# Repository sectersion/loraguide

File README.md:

# loraguide

Hello! In this guide, you will create a custom Meshtastic-enabled LORA board with a microcontroller, antenna, radio chip, and other things.

## First things first

To start your project, we need to download KiCad. KiCad is an open-source software for designing circuit boards, or PCBs. We can use the terms interchangably.

Go to https://www.kicad.org/download/ and install the version for your OS. After that finishes, create a new project. Name it anything you want, but I will name mine Loraguide.

After that finishes, you should be on a screen that looks like this: 

# The Schematic

The first step to designing a circuit board is the schematic. A schematic is essentially a wiring diagram, to show which components connect to what. That means it is very important that we follow a few design rules when creating our schematic:

 - Power symbols always point up
 - Ground symbols always point down
 - Net labels can be used instead of wires

First, click **Schematic Editor** on the main project page. Hit the **A** key to open the symbol chooser. Search "esp32-s3" and select the **ESP32-S3-WROOM-1**.

Place it in the middle. Next, search for the **SX1262** radio chip and place it to the left of the ESP32.

## Power system

### Organization
To keep things clean, use **Power Symbols** instead of drawing wires everywhere. Hit **P**, type +3V3, and place it on the 3V3 pin of the ESP32. Do the same for GND.

### Power input
Search for "USB_C_Receptacle_USB2.0_14P". 

Connect the GND pins to a GND power symbol. **Note on the SHIELD pins:** Do not connect these directly to GND. This can feed RF noise back into your host computer. For this project, leave the shield pins isolated or connected to a separate chassis pad if available.

Connect **VBUS** to a **+5V** power symbol. Place two **5.1k ohm** resistors (R_Small) on the **CC1** and **CC2** pins and connect the other ends to GND. This ensures your USB-C charger provides the correct 5V.

## SX1262 Power & RF

### Power Decoupling
Chips draw sudden bursts of current. Decoupling capacitors (100nF and 10µF) act as local water tanks, sitting right next to the chip to handle these bursts.

Connect **VDD_IN** to **+3V3** and place one **100nF** and one **10µF** capacitor between that line and GND.

### The DCC_SW Inductor
The SX1262 has an internal DC-DC converter that requires a **15µH inductor** on the **DCC_SW** pin. This inductor needs special care; it is a switching component right next to the radio. On the PCB, it must be placed as close as possible to the pin.

### RF Output Matching
Simply running a wire to the antenna is inefficient and can be illegal because it emits harmonics. You need a **matching network** (filtering) on the RF output. This usually involves a series inductor and capacitors to GND between the **RFO** pin and the antenna connector.

| Pin | What to do: |
|---|---|
| VDD_IN | Decouple with 100nF and 10µF |
| VBAT | Draw a direct wire to VDD_IN |
| VBAT_IO | Decouple with one 100nF capacitor |
| VREG | Decouple with one 100nF capacitor |
| DCC_SW | Connect 15µH inductor |
| VR_PA | 100nF capacitor to GND (DO NOT connect to 3.3V) |
| GND | Connect directly to GND |

### 5V to 3.3V conversion
Use an **AMS1117-3.3** LDO regulator to convert the 5V from USB to the 3.3V our chips need.

| Pin | Connection |
|-----|-----------|
| VIN | +5V from VBUS + 10µF cap to GND |
| VOUT | +3V3 + 10µF cap to GND |
| GND | GND |

## USB Data, Buttons, and SPI

### USB Data Lines
Connect the **D+** and **D-** pins of the USB connector to the **USB Data + and -** pins on the ESP32. Use **Net Labels (L)** to keep the wires from crossing.

### Boot and Reset Buttons
Both the **EN** (Reset) and **GPIO0** (Boot) pins need a **10kΩ pull-up resistor** to 3.3V. Connect push buttons that pull these pins to GND when pressed.

### SPI & Control Wiring
| Signal | ESP32 Pin | SX1262 Pin |
|--------|-----------|------------|
| SCK    | GPIO5     | SCK        |
| MOSI   | GPIO6     | MOSI       |
| MISO   | GPIO7     | MISO       |
| NSS    | GPIO8     | NSS        |
| RESET  | GPIO3     | RESET      |
| BUSY   | GPIO4     | BUSY       |
| DIO1   | GPIO9     | DIO1       |

# PCB Section

## Footprint Assignment
In **Tools > Assign Footprints**, assign the physical shapes. For resistors and capacitors, **R_0402** or **C_0402** are standard for these boards.

## Placement
1. **ESP32:** Place at the top. Ensure the antenna "keep-out" area is outside the board edge.
2. **SX1262 & U.FL Connector:** Place these very close together.
3. **DCC_SW Inductor:** Place this right against the radio chip pin.
4. **Decoupling Caps:** Place them right next to their respective power pins.

## Routing Order
Sensitive signals must be routed first so they have the cleanest, most direct paths.

1. **RF Trace First:** Shortest path from chip to antenna. Use 45-degree angles.
2. **USB Data Lines:** Route D+ and D- as a pair, keeping them similar in length.
3. **SPI & Control Signals:** Connect the communication lines.
4. **Power Traces:** 3.3V and 5V. Use wider traces (0.5mm) for these.
5. **GND:** Handled by the copper pour.

## Ground Plane and Stitching
Add a **Filled Zone (Z)** for GND on both the top (**F.Cu**) and bottom (**B.Cu**) layers. 

To prevent "floating" ground islands and interference, add **stitching vias**. These are small holes that connect the top and bottom ground planes. Place them around the perimeter of the board and near the RF trace.

## Final Steps
Run the **DRC (Design Rule Check)** to find errors. Export your **Gerbers** and **Drill Files**, zip them up, and upload to a manufacturer like JLCPCB.

You have designed a grounded and RF-safe LoRa board.

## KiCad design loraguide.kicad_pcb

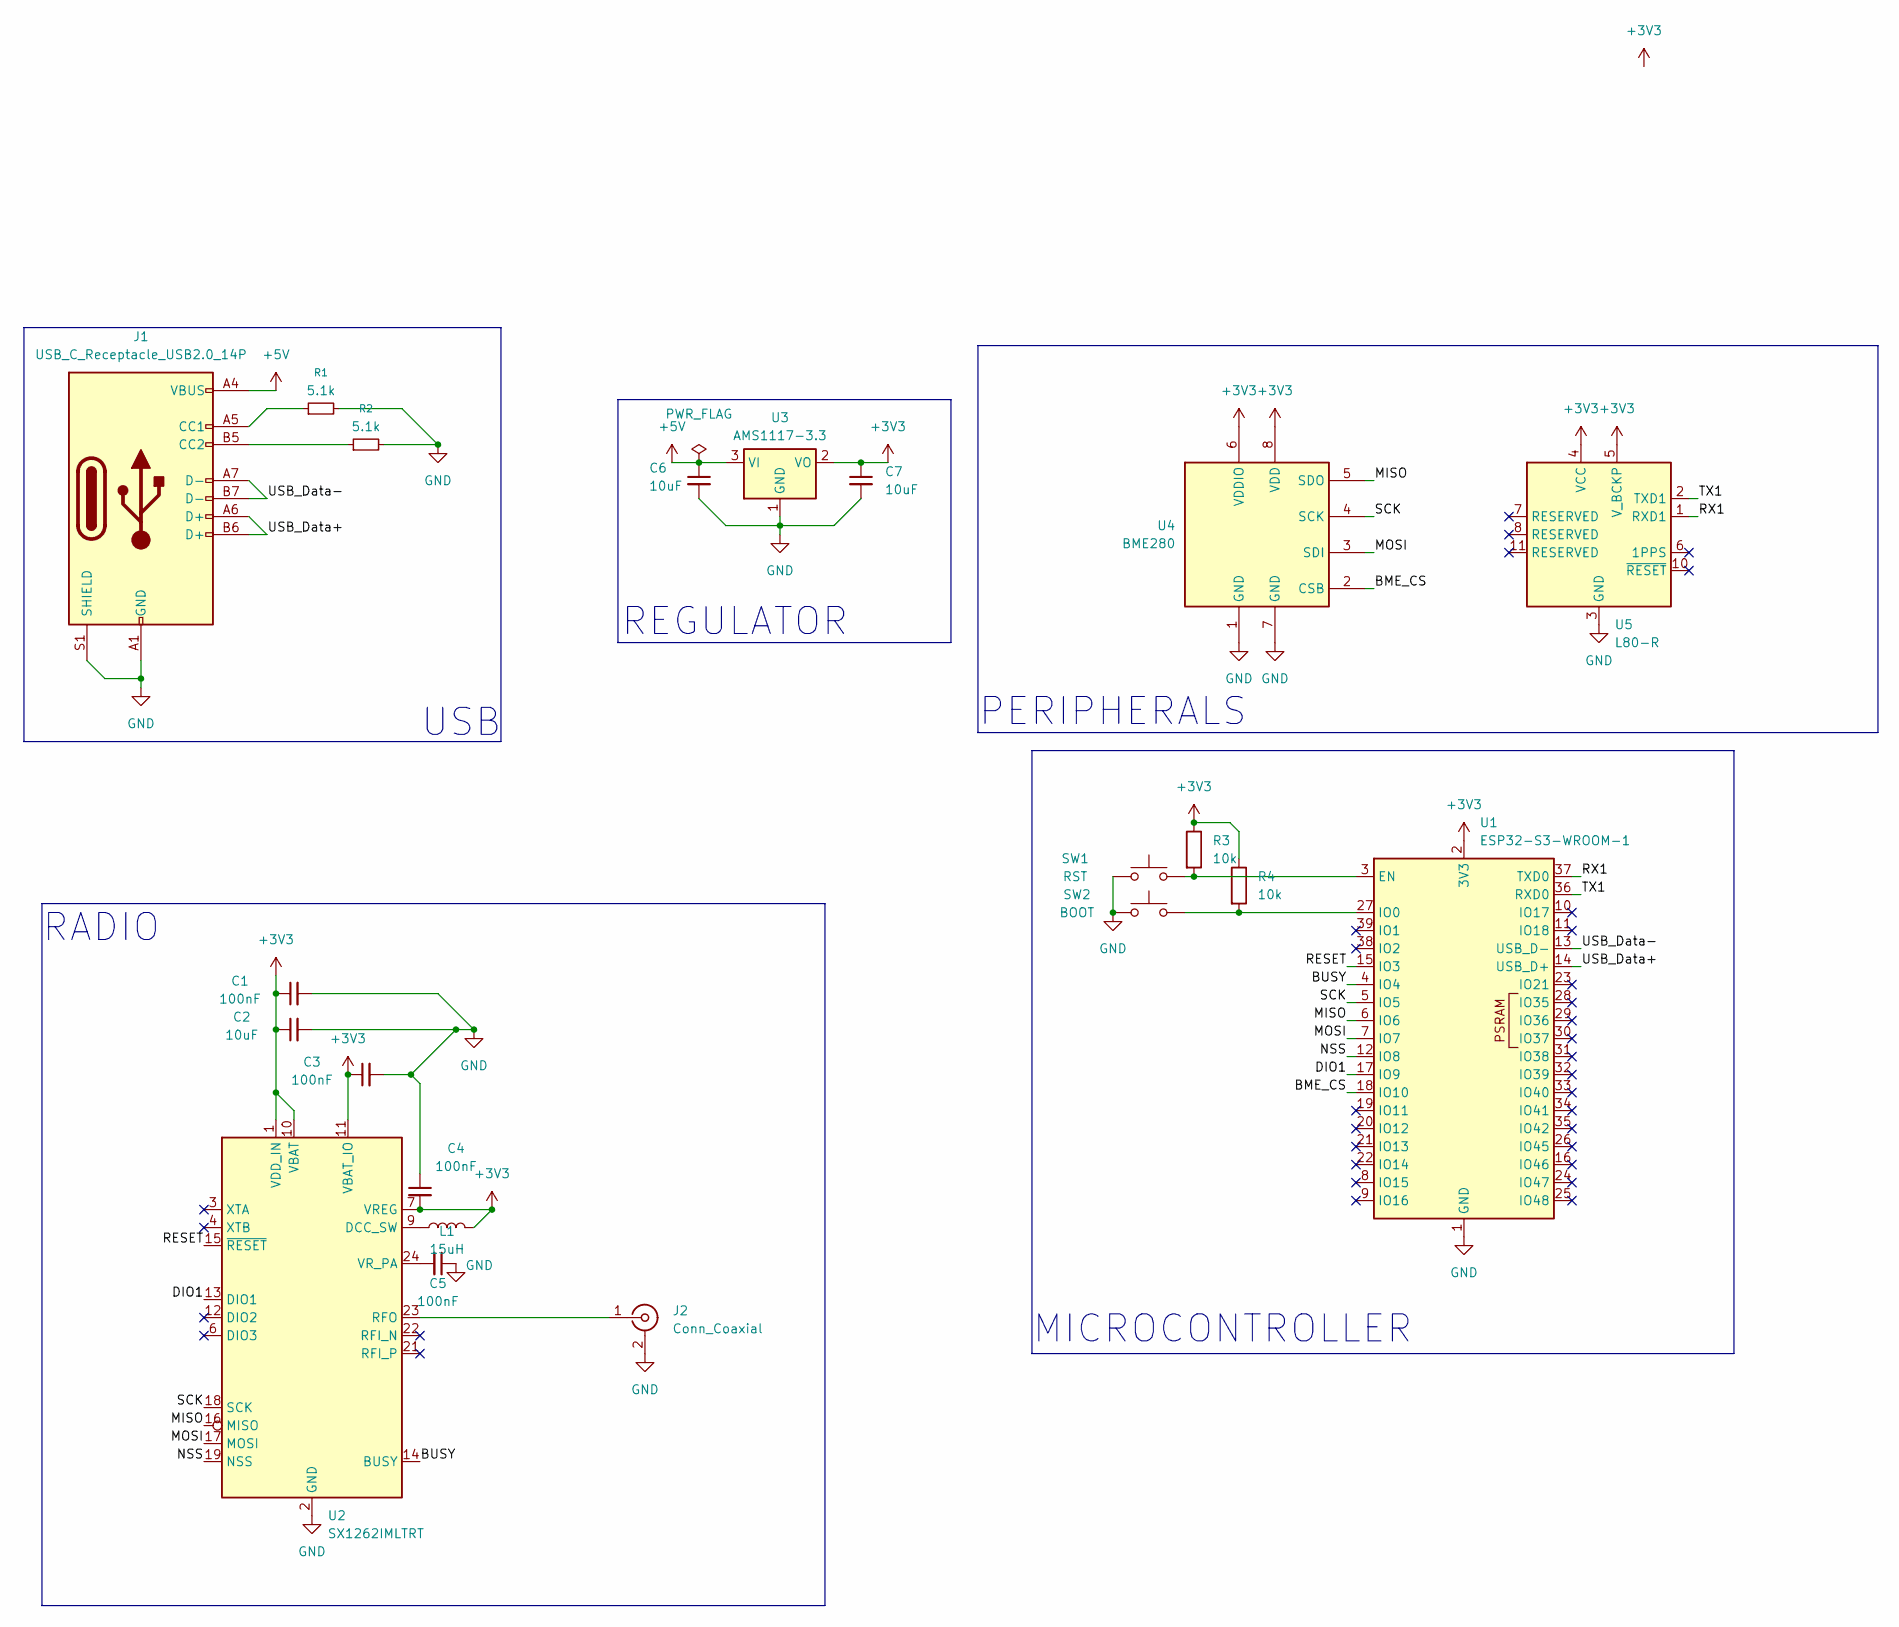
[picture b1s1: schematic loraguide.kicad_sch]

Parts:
C1, C3, C4, C5: 100nF; C_0402_1005Metric
C2, C6, C7: 10uF; C_0402_1005Metric
J1: USB_C_Receptacle_USB2.0_14P; USB_C_Receptacle_GCT_USB4085
J2: Conn_Coaxial; U.FL_Hirose_U.FL-R-SMT-1_Vertical
L1: 15uH; L_0603_1608Metric
R1, R2: 5.1k; R_0402_1005Metric
R3, R4: 10k; R_0402_1005Metric
SW1: RST; SW_SPST_B3U-1000P
SW2: BOOT; SW_SPST_B3U-1000P
U1: ESP32-S3-WROOM-1
U2: SX1262IMLTRT; QFN-24-1EP_4x4mm_P0.5mm_EP2.6x2.6mm
U3: AMS1117-3.3; SOT-223-3_TabPin2
U4: BME280; Bosch_LGA-8_2.5x2.5mm_P0.65mm_ClockwisePinNumbering
U5: L80-R; Quectel_L80-R

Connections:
+3V3: C1.1, C2.1, C3.1, C4.2, C7.1, L1.2, R3.1, R4.1, U1.2 (3V3), U2.1 (VDD_IN), U2.7 (VREG), U2.10 (VBAT), U2.11 (VBAT_IO), U3.2 (VO), U4.6 (VDDIO), U4.8 (VDD), U5.4 (VCC), U5.5 (V_BCKP)
+5V: C6.1, J1.A4 (VBUS), J1.A9 (VBUS), J1.B4 (VBUS), J1.B9 (VBUS), U3.3 (VI)
/BME_CS: U1.18 (IO10), U4.2 (CSB)
/BUSY: U1.4 (IO4), U2.14 (BUSY)
/DIO1: U1.17 (IO9), U2.13 (DIO1)
/MISO: U1.6 (IO6), U2.16 (MISO), U4.5 (SDO)
/MOSI: U1.7 (IO7), U2.17 (MOSI), U4.3 (SDI)
/NSS: U1.12 (IO8), U2.19 (NSS)
/RESET: U1.15 (IO3), U2.15 (~RESET)
/RX1: U1.37 (TXD0), U5.1 (RXD1)
/SCK: U1.5 (IO5), U2.18 (SCK), U4.4 (SCK)
/TX1: U1.36 (RXD0), U5.2 (TXD1)
/USB_Data+: J1.A6 (D+), J1.B6 (D+), U1.14 (USB_D+)
/USB_Data-: J1.A7 (D-), J1.B7 (D-), U1.13 (USB_D-)
GND: C1.2, C2.2, C3.2, C4.1, C5.1, C6.2, C7.2, J1.A1 (GND), J1.A12 (GND), J1.B1 (GND), J1.B12 (GND), J1.S1 (SHIELD), J2.2 (Ext), R1.2, R2.2, SW1.1, SW2.1, U1.1 (GND), U1.40 (GND), U1.41 (GND), U2.2 (GND), U2.5 (GND), U2.8 (GND), U2.20 (GND), U2.25 (GND), U3.1 (GND), U4.1 (GND), U4.7 (GND), U5.3 (GND), U5.12 (GND)
unnamed: J1.A5 (CC1), R1.1
unnamed: J1.B5 (CC2), R2.1
unnamed: J2.1 (In), U2.23 (RFO)
unnamed: R3.2, SW1.2, U1.3 (EN)
unnamed: R4.2, SW2.2, U1.27 (IO0)
unnamed: L1.1, U2.9 (DCC_SW)
unnamed: C5.2, U2.24 (VR_PA)

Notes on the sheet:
RADIO
PERIPHERALS
REGULATOR
USB
MICROCONTROLLER

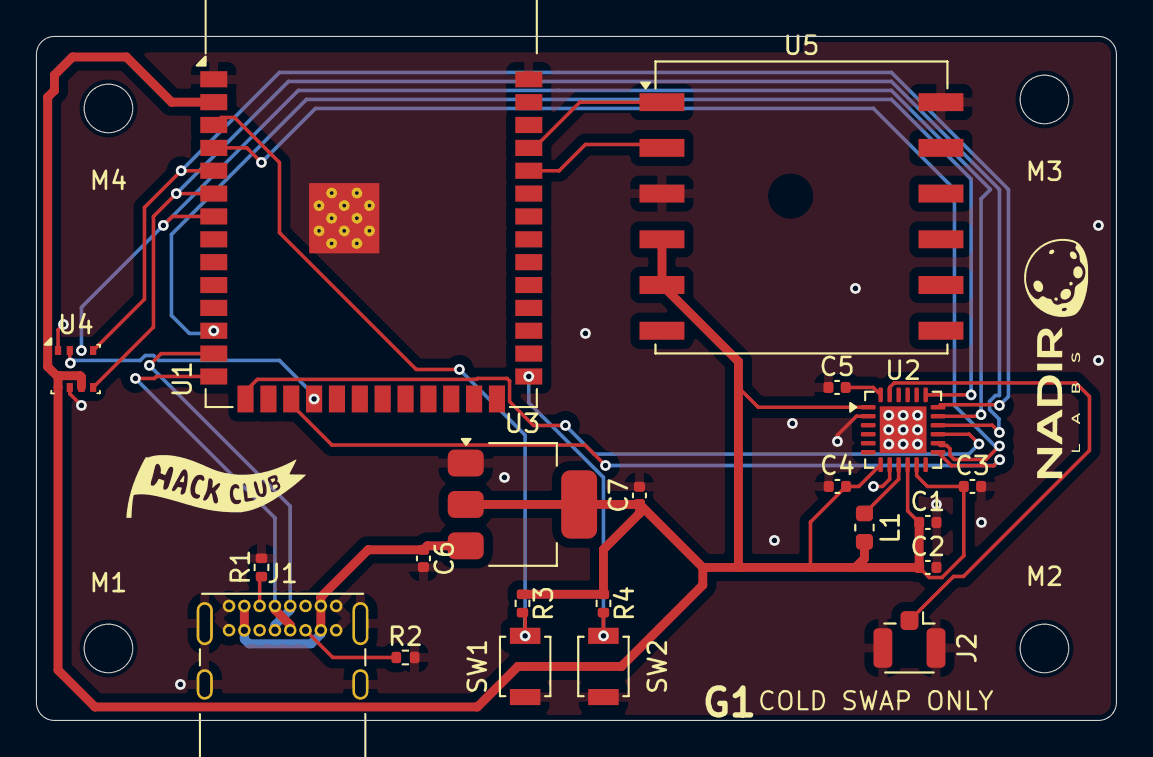
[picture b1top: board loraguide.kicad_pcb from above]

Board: 2 copper layers, 60.0 x 38.0 mm, 27 parts (0 on the bottom side), 22 nets.

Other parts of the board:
G1: LOGO; nl_bw_large
G2: LOGO; hc_bw_small
M1, M2, M3, M4: MountingHole_2.7mm_M2.5

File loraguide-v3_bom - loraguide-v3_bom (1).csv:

Designator,Footprint,Quantity,Value,LCSC Part #
"C1, C3, C4, C5",402,4,100nF,C60474
"C2, C6, C7",402,3,10uF,C315248
J1,USB_C_Receptacle_GCT_USB4085,1,USB_C_Receptacle_USB2.0_14P,C7095263
J2,U.FL_Hirose_U.FL-R-SMT-1_Vertical,1,Conn_Coaxial,C434808
L1,603,1,15uH,C486329
"R1, R2",402,2,5.1k,C105872
"R3, R4",402,2,10k,C60490
SW1,SW_SPST_B3U-1000P,1,RST,C231329
SW2,SW_SPST_B3U-1000P,1,BOOT,C231329
U1,ESP32-S3-WROOM-1,1,ESP32-S3-WROOM-1,C2913197
U2,QFN-24-1EP_4x4mm_P0.5mm_EP2.6x2.6mm,1,SX1262IMLTRT,C191341
U3,SOT-223-3_TabPin2,1,AMS1117-3.3,C6186
U4,Bosch_LGA-8_2.5x2.5mm_P0.65mm_ClockwisePinNumbering,1,BME280,C92489

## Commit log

2026-03-21 Expand README with KiCad setup and schematic guidance
    Added detailed instructions for setting up KiCad and creating a schematic for the LORA board project, including design rules and component placement.
2026-03-22 finish schematic
2026-03-22 finish schematic section
    Updated the README to include detailed instructions on circuit board design, power input, and component connections for the ESP32 and SX1262.
2026-03-22 finish readme
2026-03-22 finished pcb upload + gerbers
2026-03-22 upload step
2026-04-08 upload
